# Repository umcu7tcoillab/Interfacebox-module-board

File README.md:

# Interfacebox module board

## About us
This design has been made by the coil-lab of the High Field MRI Group of the UMC Utrecht in the Netherlands, where we make hardware to support our researchers. We are part of a research group which means we feel the need to open up some of our designs to whomever can make use of it, to further the research of MRI applications.

## The design
This project contains a interfacebox module board made to be used with our driverboard, malfunctionboard and preamp board for our 7T Philips Achieva MRI system. It has been tested inside the magnetic field of the 7T MRI. 

The module board is designed to facilitate the making of an interfacebox, using our custom made PCB's. All the different modules can be attached to this board, making it act as an interfacebox.
There is an option to choose between 8 or 16 channels.

The design and subsequent drawing has been done in Kicad 5.1.5.

## Download
Gerber and BOM production files for the latest _field tested_ version of the PCB can be found in the 'Releases' page, or by following [this link](https://github.com/umcu7tcoillab/Interfacebox-module-board/releases/latest). 
You can also make your own production files by downloading the Kicad project and generating them, but these are not guaranteed to have been field tested.

## Images
**3D Image**

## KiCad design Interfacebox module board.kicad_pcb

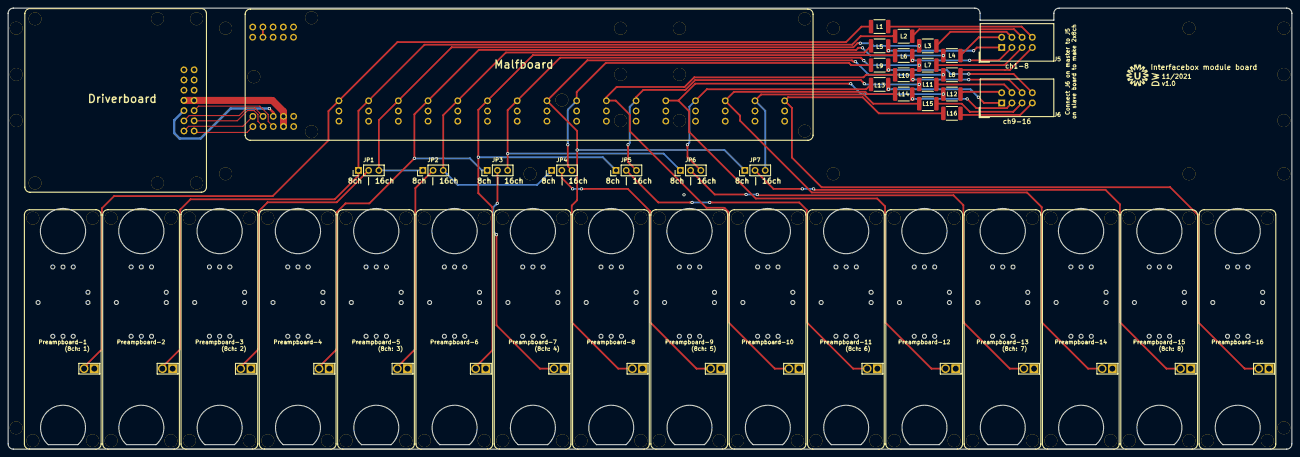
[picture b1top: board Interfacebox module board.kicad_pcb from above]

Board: 2 copper layers, 319.7 x 109.8 mm, 58 parts (0 on the bottom side), 48 nets.

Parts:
G1: UMC_logo; UMC_logo_small
H1, H2, H4, H6, H10, H11, H12, H13, H14, H15: MH_Pad; MountingHole_3.2mm_M3_plated
J4: Driverboard
J5: 1-8; IDC-Header_2x04_P2.54mm_Vertical
J6: 9-16; IDC-Header_2x04_P2.54mm_Vertical
JP1, JP2, JP3, JP4, JP5, JP6, JP7: Jumper; PinHeader_1x03_P2.54mm_Vertical
L1, L2, L3, L4, L5, L6, L7, L8, L9, L10, L11, L12, L13, L14, L15, L16: choke; L_1812_4532Metric
MB1: Malfboard; Malfunctionboard
Preampboard-1, Preampboard-2, Preampboard-3, Preampboard-4, Preampboard-5, Preampboard-6, Preampboard-7, Preampboard-8, Preampboard-9, Preampboard-10, Preampboard-11, Preampboard-12, Preampboard-13, Preampboard-14, Preampboard-15, Preampboard-16: Preampboard
SYM3, SYM4, SYM5, SYM6: RXE4

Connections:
+12V: J4.5, MB1.B5
-5V: J4.6, MB1.B6
GND: H1.1, H2.1, H4.1, H6.1, H10.1, H11.1, H12.1, H13.1, H14.1, H15.1, J4.9, J4.10, J4.11, J4.12, MB1.1, MB1.B9, MB1.B10, MB1.T9, MB1.T10, Preampboard-1.1, Preampboard-2.1, Preampboard-3.1, Preampboard-4.1, Preampboard-5.1, Preampboard-6.1, Preampboard-7.1, Preampboard-8.1, Preampboard-9.1, Preampboard-10.1, Preampboard-11.1, Preampboard-12.1, Preampboard-13.1, Preampboard-14.1, Preampboard-15.1, Preampboard-16.1, SYM3.1, SYM4.1, SYM5.1, SYM6.1
Malf: J4.4, MB1.B4
Malf_MH: J4.3, MB1.B3
unnamed: J5.1, L5.1
unnamed: J5.2, L4.1
unnamed: J5.3, L6.1
unnamed: J5.4, L3.1
unnamed: J5.5, L7.1
unnamed: J5.6, L2.1
unnamed: J5.7, L8.1
unnamed: J5.8, L1.1
unnamed: J6.1, L13.1
unnamed: J6.2, L12.1
unnamed: J6.3, L14.1
unnamed: J6.4, L11.1
unnamed: J6.5, L15.1
unnamed: J6.6, L10.1
unnamed: J6.7, L16.1
unnamed: J6.8, L9.1
unnamed: JP1.1, L2.2, MB1.Rx2, Preampboard-2.2
unnamed: JP1.2, Preampboard-3.2
unnamed: JP1.3, JP2.1, L3.2, MB1.Rx3
unnamed: JP2.2, Preampboard-5.2
unnamed: JP2.3, JP4.1, L5.2, MB1.Rx5
unnamed: JP3.1, L4.2, MB1.Rx4, Preampboard-4.2
unnamed: JP3.2, Preampboard-7.2
unnamed: JP3.3, JP6.1, L7.2, MB1.Rx7
unnamed: JP4.2, Preampboard-9.2
unnamed: JP4.3, L9.2, MB1.Rx9
unnamed: JP5.1, L6.2, MB1.Rx6, Preampboard-6.2
unnamed: JP5.2, Preampboard-11.2
unnamed: JP5.3, L11.2, MB1.Rx11
unnamed: JP6.2, Preampboard-13.2
unnamed: JP6.3, L13.2, MB1.Rx13
unnamed: JP7.1, L8.2, MB1.Rx8, Preampboard-8.2
unnamed: JP7.2, Preampboard-15.2
unnamed: JP7.3, L15.2, MB1.Rx15
unnamed: L1.2, MB1.Rx1, Preampboard-1.2
unnamed: L10.2, MB1.Rx10, Preampboard-10.2
unnamed: L12.2, MB1.Rx12, Preampboard-12.2
unnamed: L14.2, MB1.Rx14, Preampboard-14.2
unnamed: L16.2, MB1.Rx16, Preampboard-16.2
unnamed: MB1.T3, MB1.T4
Ref_V+: J4.2, MB1.B2
Ref_V-: J4.1, MB1.B1
detune_in: J4.7, J4.8, MB1.B7, MB1.B8

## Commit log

2020-02-25 Added: connectors to distribute 16ch to 2 boards
2020-02-25 Added: slot for ribbon cable
2020-02-25 Changed: comments; README. Added: 3D render
2020-02-26 Changed: Removed unnecessary references in file
2020-03-05 Added: holes for preamp socket pins, via's. Changed: 3D settings
2020-03-05 New 3D image
2020-03-05 Updated LICENSE
2020-03-12 Added: outisde diameter
2020-03-13 Added: mounting holes for 2 RXE4's
2020-03-18 Changed: better and new footprint for malfunctionboard
2020-03-19 Updated: preamp footprint to accommodate preci-dip connectors. Added: some GND via's
2020-03-19 Added: missing logo
2021-11-24 Small changes. V0.3
2021-11-24 v0.3
2021-11-24 Updated to v1.0
